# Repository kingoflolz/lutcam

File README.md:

# LUTCam - FPGA image fiducial detection

**Note, this repo is just a snapshot of a side project. Don't expect any support or new features.**

**All the software/RTL is AI generated, but it does work ¯\\\_(ツ)\_/¯**

See blog post describing this project [here](https://benwang.dev/2026/11/01/FPGA-Fiducial.html).

LUTCam's original RTL/gateware, software, firmware, and hardware designs are
licensed under the [Apache License, Version 2.0](LICENSE). See [NOTICE](NOTICE)
for the scope and [THIRD_PARTY_NOTICES.md](THIRD_PARTY_NOTICES.md) for third-party
code, library elements, models, documentation, and data that retain their own terms.

The project is organized into three directories:

| Directory | Contents |
| --- | --- |
| [software](software/) | Camera viewer, reusable Rust libraries, and their software tests |
| [hardware](hardware/) | KiCad board and schematics, local libraries, 3D models, and datasheets |
| [gateware](gateware/) | Production RTL, FPGA targets, Rust reference models and RTL tests, Python simulations, board tools, fixtures, and design documentation |

One root `Cargo.toml` and `Cargo.lock` cover both software and gateware crates.
The default members are the four software crates; RTL verification crates are
selected explicitly or with `--workspace`.

Run these commands from the repository root:

```sh
cargo run --locked -p lutcam-viewer --release
cargo test --locked                                      # Software tests
cargo test --locked -p lrcca-rtl-tests -- --test-threads=1 # LRCCA RTL tests
cargo test --locked --workspace -- --test-threads=1       # All Rust tests
```

Run FPGA builds, Python board helpers, and HDL checks from `gateware`.
See the [gateware guide](gateware/README.md),
[board build setup](gateware/README.md#toolchain), and
[viewer guide](software/crates/lutcam-viewer/README.md).
Open [hardware/lutcam-hardware.kicad_pro](hardware/lutcam-hardware.kicad_pro)
in KiCad to work on the board.

The software and gateware directories depend on each other; keep them as
siblings. The LiteX Python environment is defined in `gateware/pyproject.toml`
and `gateware/uv.lock`; run `uv sync --locked` from `gateware` to create it.
LUNA, its LiteX wrapper, and LiteEth are vendored with the required fixes under
`gateware/vendor`; the build uses them by default.
The viewer uses `gateware/.venv/bin/python`
when available, otherwise `python3`.

Version control contains the current sources, dependency locks, required ROM
tables, test fixtures, component models, and design documentation. Build products,
captures, benchmark output, fabrication exports, historical snapshots, editor
state, and backups are local artifacts excluded by `.gitignore`.

Repository paths are relative to the documented working directory or resolved
from the calling script's location. Set `EFINITY_HOME` (or `LITEX_ENV_EFINITY`
for LiteX) to your external Efinity installation when running native FPGA tools
or vendor-model tests.

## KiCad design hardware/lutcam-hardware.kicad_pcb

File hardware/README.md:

# Lutcam hardware

Open `lutcam-hardware.kicad_pro` in KiCad to work on the board and schematics.
The [datasheet inventory](datasheets/README.md) and
[3D model provenance](models3d/README.md) describe the supporting assets.

## License

Lutcam's original hardware design files, including schematics, PCB layout,
original symbols and footprints, and original mechanical models, are licensed
under the [Apache License, Version 2.0](../LICENSE).

Third-party library elements, supplier models, and manufacturer documentation
retain their own terms, including when embedded in a design or converted to
another format. See [NOTICE](../NOTICE) and
[THIRD_PARTY_NOTICES.md](../THIRD_PARTY_NOTICES.md) for the scope and exceptions.

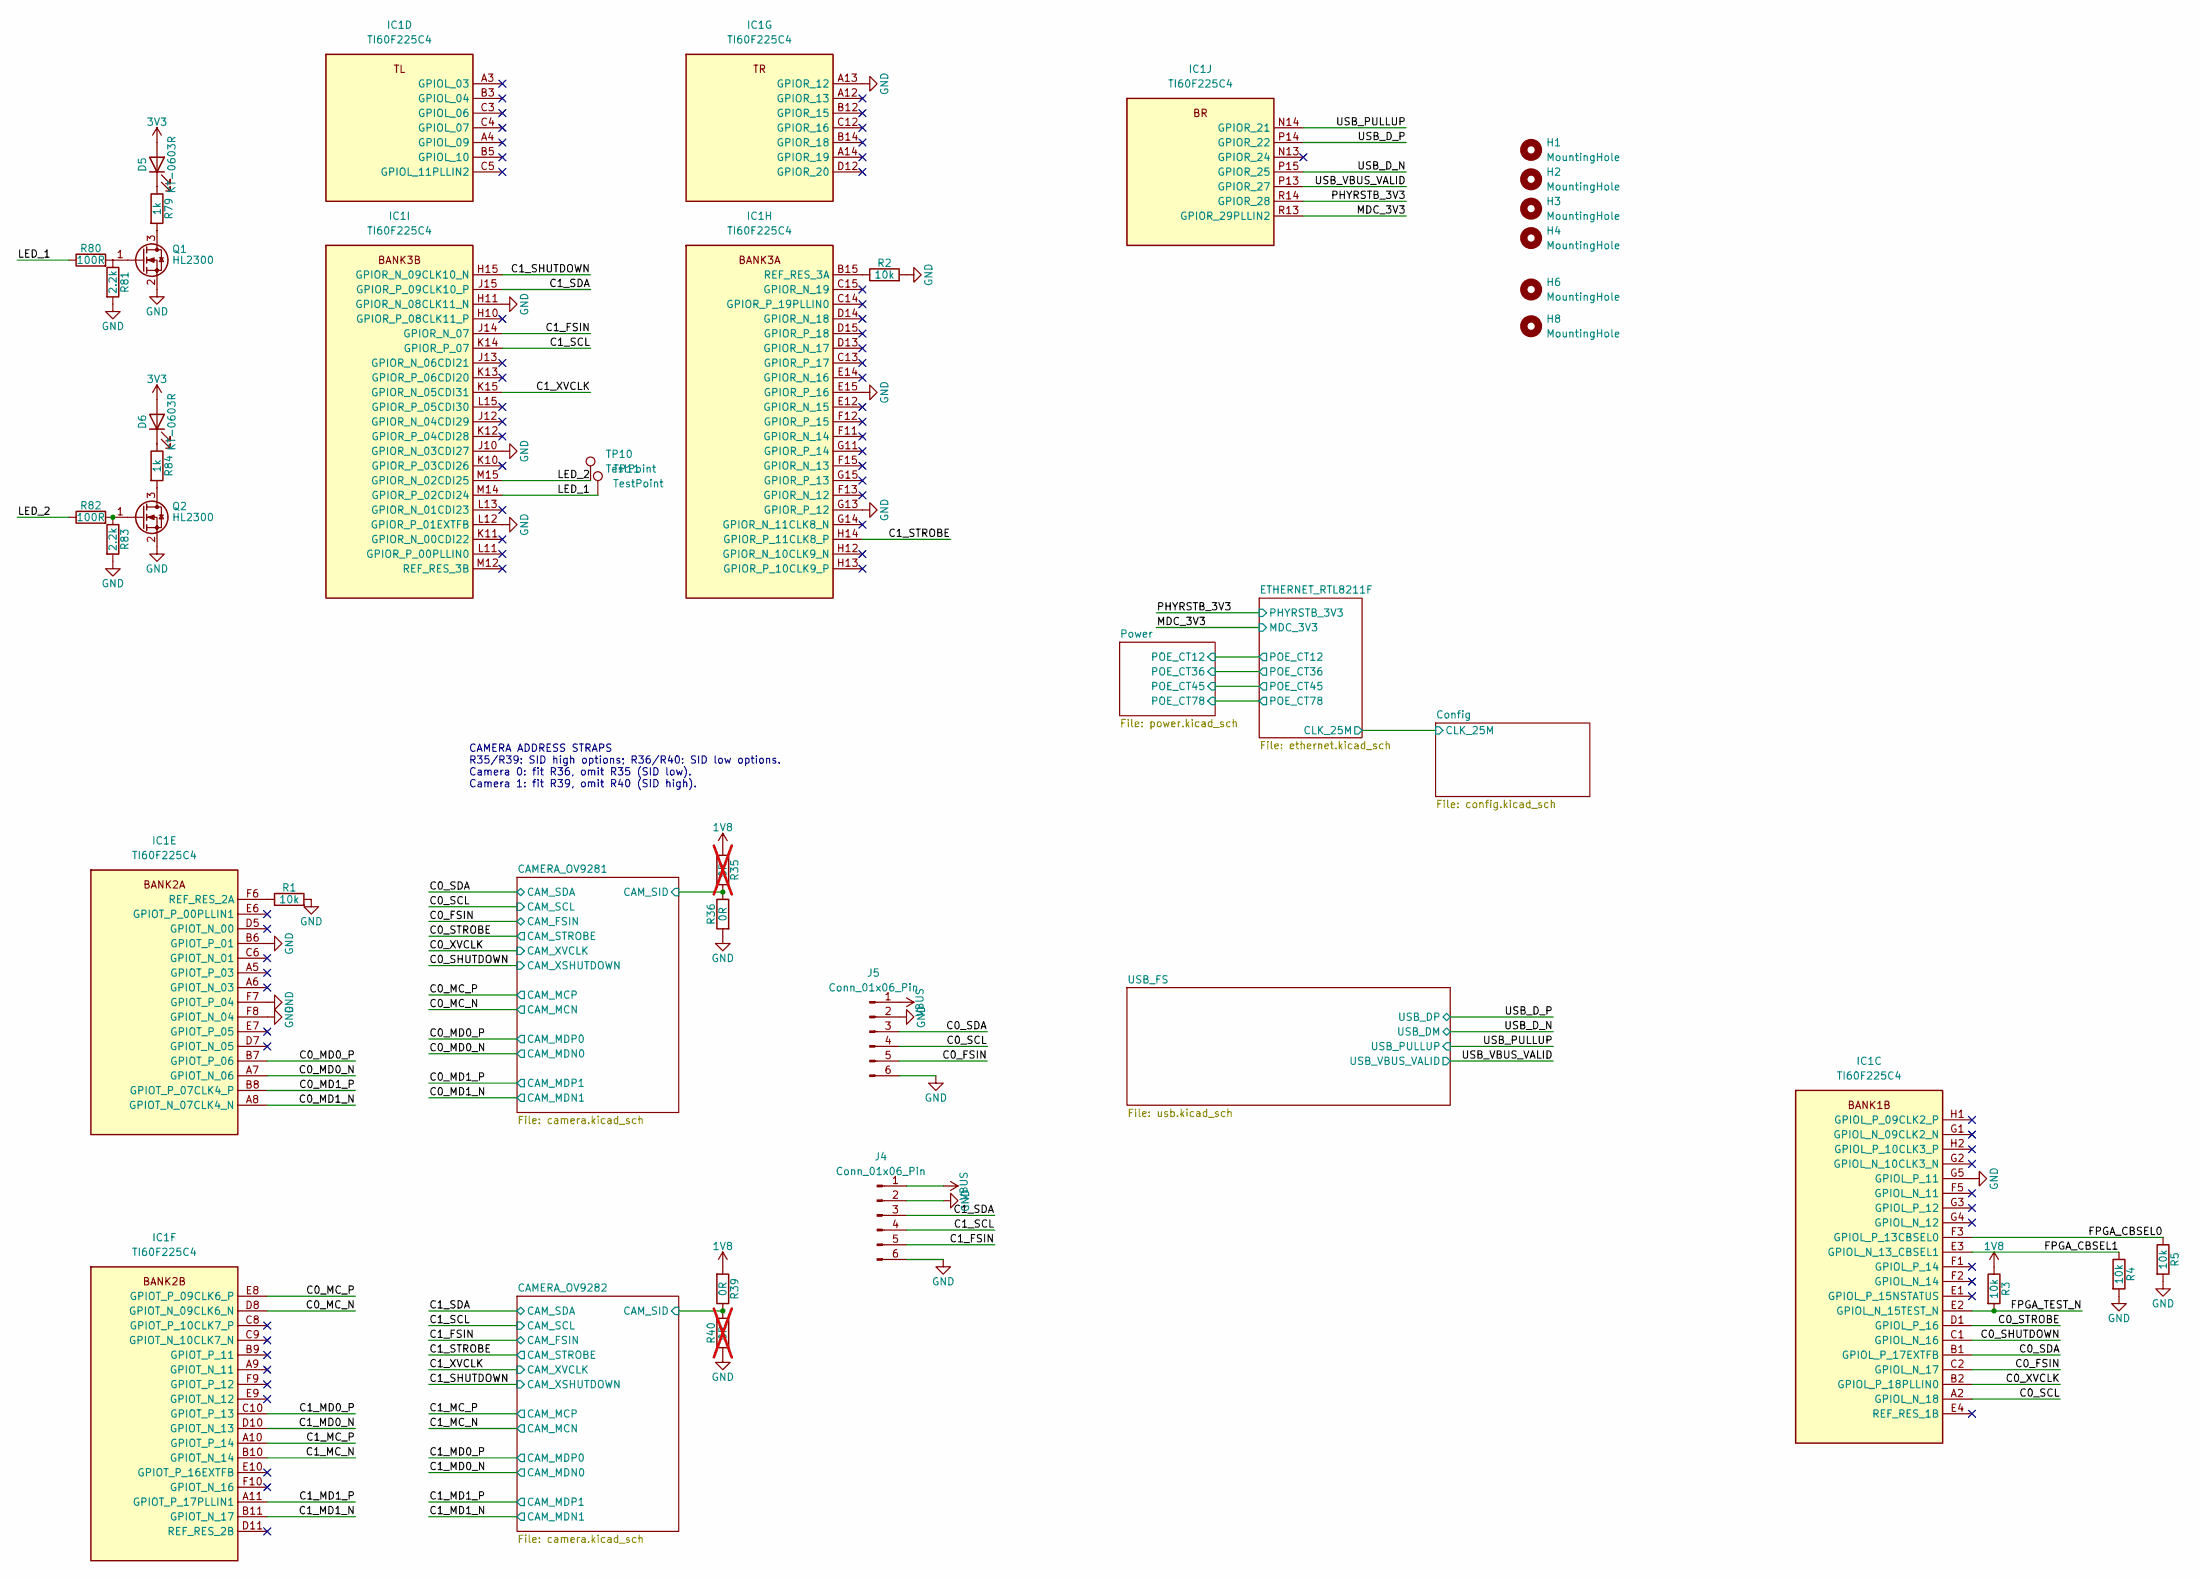
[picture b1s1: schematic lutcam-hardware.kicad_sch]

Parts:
D5, D6: KT-0603R; LED_0603_1608Metric; MPN KT-0603R; JLCPCB Library Basic
H1, H2, H3, H4, H6: MountingHole; MountingHole_2.2mm_M2_Pad_Via
H8: MountingHole; ToolingHole_1.152mm
IC1: TI60F225C4; BGA225C65P15X15_1000X1000X100; Manufacturer_Part_Number TI60F225C4
J4, J5: Conn_01x06_Pin; PinHeader_1x06_P2.54mm_Vertical
Q1, Q2: HL2300; SOT-23; MPN HL2300; JLCPCB Library Promotional Extended
R1, R2, R3, R4, R5: 10k; R_0402_1005Metric; MPN 0402WGF1002TCE; JLCPCB Library Basic
R35, R40: 0R; R_0402_1005Metric; MPN 0402WGF0000TCE; JLCPCB Library Basic; not fitted
R36, R39: 0R; R_0402_1005Metric; MPN 0402WGF0000TCE; JLCPCB Library Basic
R79, R84: 1k; R_0402_1005Metric; MPN 0402WGF1001TCE; JLCPCB Library Basic
R80, R82: 100R; R_0402_1005Metric; MPN 0402WGF1000TCE; JLCPCB Library Basic
R81, R83: 2.2k; R_0402_1005Metric; MPN 0402WGF2201TCE; JLCPCB Library Basic
TP10, TP11: TestPoint; TestPoint_Pad_D2.0mm

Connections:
1V8: R3.1, R35.2, R39.2; also elsewhere on the board
3V3: D5.2 (A), D6.2 (A); also elsewhere on the board
/C0_FSIN: IC1.C2 (GPIOL_N_17), J5.5; also elsewhere on the board
/C0_MC_N: IC1.D8 (GPIOT_N_09CLK6_N); also elsewhere on the board
/C0_MC_P: IC1.E8 (GPIOT_P_09CLK6_P); also elsewhere on the board
/C0_MD0_N: IC1.A7 (GPIOT_N_06); also elsewhere on the board
/C0_MD0_P: IC1.B7 (GPIOT_P_06); also elsewhere on the board
/C0_MD1_N: IC1.A8 (GPIOT_N_07CLK4_N); also elsewhere on the board
/C0_MD1_P: IC1.B8 (GPIOT_P_07CLK4_P); also elsewhere on the board
/C0_SCL: IC1.A2 (GPIOL_N_18), J5.4; also elsewhere on the board
/C0_SDA: IC1.B1 (GPIOL_P_17EXTFB), J5.3; also elsewhere on the board
/C0_SHUTDOWN: IC1.C1 (GPIOL_N_16); also elsewhere on the board
/C0_STROBE: IC1.D1 (GPIOL_P_16); also elsewhere on the board
/C0_XVCLK: IC1.B2 (GPIOL_P_18PLLIN0); also elsewhere on the board
/C1_FSIN: IC1.J14 (GPIOR_N_07), J4.5; also elsewhere on the board
/C1_MC_N: IC1.B10 (GPIOT_N_14); also elsewhere on the board
/C1_MC_P: IC1.A10 (GPIOT_P_14); also elsewhere on the board
/C1_MD0_N: IC1.D10 (GPIOT_N_13); also elsewhere on the board
/C1_MD0_P: IC1.C10 (GPIOT_P_13); also elsewhere on the board
/C1_MD1_N: IC1.B11 (GPIOT_N_17); also elsewhere on the board
/C1_MD1_P: IC1.A11 (GPIOT_P_17PLLIN1); also elsewhere on the board
/C1_SCL: IC1.K14 (GPIOR_P_07), J4.4; also elsewhere on the board
/C1_SDA: IC1.J15 (GPIOR_P_09CLK10_P), J4.3; also elsewhere on the board
/C1_SHUTDOWN: IC1.H15 (GPIOR_N_09CLK10_N); also elsewhere on the board
/C1_STROBE: IC1.H14 (GPIOR_P_11CLK8_P); also elsewhere on the board
/C1_XVCLK: IC1.K15 (GPIOR_N_05CDI31); also elsewhere on the board
/CAMERA_OV9281/CAM_SID: R35.1, R36.1; also elsewhere on the board
/CAMERA_OV9282/CAM_SID: R39.1, R40.1; also elsewhere on the board
/FPGA_CBSEL0: IC1.F3 (GPIOL_P_13CBSEL0), R5.1
/FPGA_CBSEL1: IC1.E3 (GPIOL_N_13_CBSEL1), R4.1
/FPGA_TEST_N: IC1.E2 (GPIOL_N_15TEST_N), R3.2
/LED_1: IC1.M14 (GPIOR_P_02CDI24), R80.1, TP11.1 (1_1)
/LED_2: IC1.M15 (GPIOR_N_02CDI25), R82.1, TP10.1 (1_1)
/MDC_3V3: IC1.R13 (GPIOR_29PLLIN2); also elsewhere on the board
/PHYRSTB_3V3: IC1.R14 (GPIOR_28); also elsewhere on the board
/USB_D_N: IC1.P15 (GPIOR_25); also elsewhere on the board
/USB_D_P: IC1.P14 (GPIOR_22); also elsewhere on the board
/USB_PULLUP: IC1.N14 (GPIOR_21); also elsewhere on the board
/USB_VBUS_VALID: IC1.P13 (GPIOR_27); also elsewhere on the board
GND: IC1.A13 (GPIOR_12), IC1.B6 (GPIOT_P_01), IC1.E15 (GPIOR_P_16), IC1.F7 (GPIOT_P_04), IC1.F8 (GPIOT_N_04), IC1.G5 (GPIOL_P_11), IC1.G13 (GPIOR_P_12), IC1.H11 (GPIOR_N_08CLK11_N), IC1.J10 (GPIOR_N_03CDI27), IC1.L12 (GPIOR_P_01EXTFB), J4.2, J4.6, J5.2, J5.6, Q1.2 (S), Q2.2 (S), R1.2, R2.2, R4.2, R5.2, R36.2, R40.2, R81.2, R83.2; also elsewhere on the board
unnamed: D5.1 (K), R79.1
unnamed: D6.1 (K), R84.1
unnamed: IC1.F6 (REF_RES_2A), R1.1
unnamed: IC1.B15 (REF_RES_3A), R2.1
unnamed: Q1.3 (D), R79.2
unnamed: Q1.1 (G), R80.2, R81.1
unnamed: Q2.3 (D), R84.2
unnamed: Q2.1 (G), R82.2, R83.1
VBUS: J4.1, J5.1; also elsewhere on the board

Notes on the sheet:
CAMERA ADDRESS STRAPS R35/R39: SID high options; R36/R40: SID low options. Camera 0: fit R36, omit R35 (SID low). Camera 1: fit R39, omit R40 (SID high).

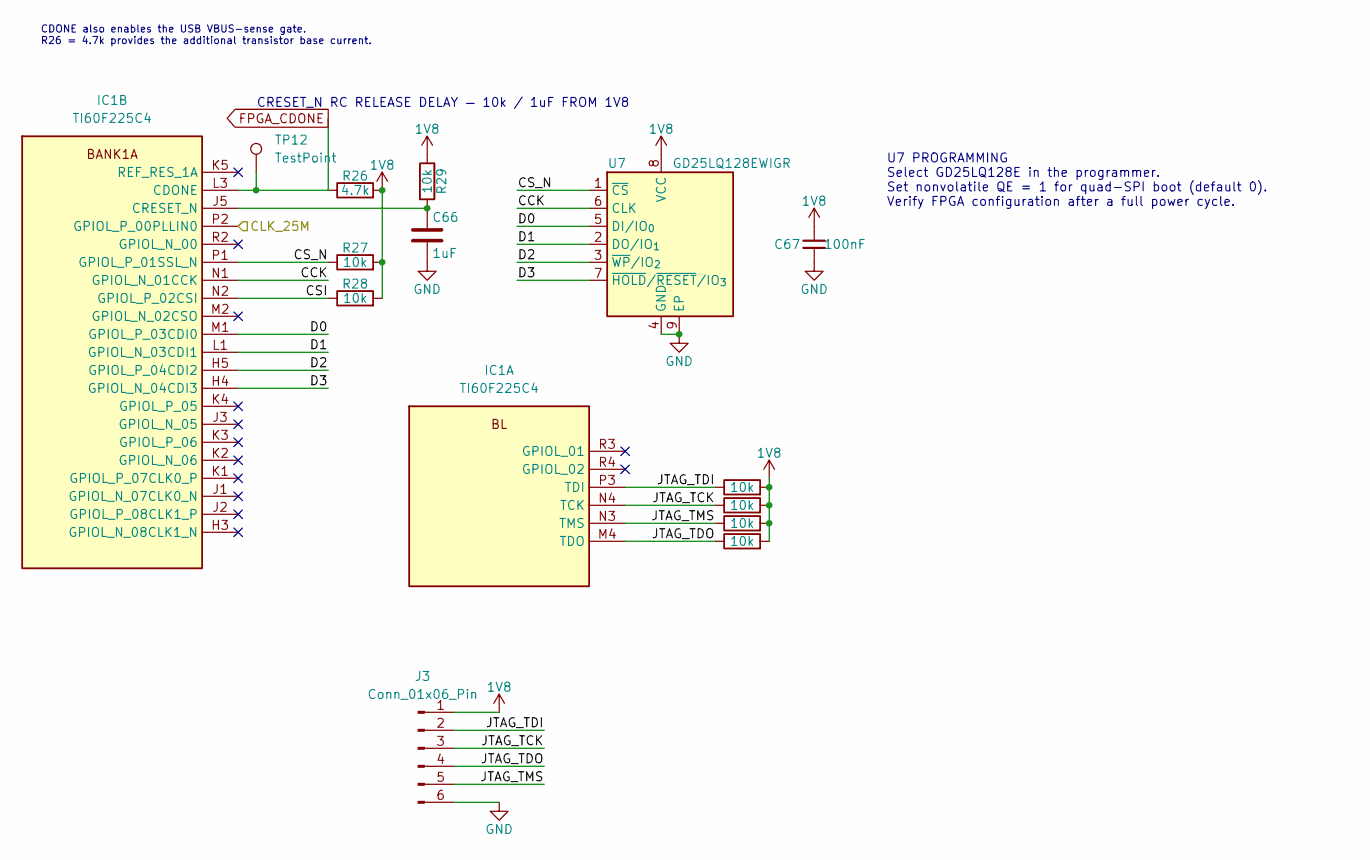
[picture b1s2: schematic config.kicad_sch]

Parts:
C66: 1uF; C_0402_1005Metric; MPN CL05A105KA5NQNC; JLCPCB Library Basic
C67: 100nF; C_0402_1005Metric; MPN CL05B104KO5NNNC; JLCPCB Library Basic
IC1: TI60F225C4; BGA225C65P15X15_1000X1000X100; Manufacturer_Part_Number TI60F225C4
J3: Conn_01x06_Pin; PinHeader_1x06_P2.54mm_Vertical
R26: 4.7k; R_0402_1005Metric; MPN 0402WGF4701TCE; JLCPCB Library Basic
R27, R28, R29, R30, R31, R32, R33: 10k; R_0402_1005Metric; MPN 0402WGF1002TCE; JLCPCB Library Basic
TP12: TestPoint; TestPoint_Pad_D2.0mm
U7: GD25LQ128EWIGR; WSON-8-1EP_6x5mm_P1.27mm_EP3.4x4.3mm; MPN GD25LQ128EWIGR; LCSC C2928889

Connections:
1V8: C67.2, J3.1, R26.2, R27.2, R28.2, R29.1, R30.2, R31.2, R32.2, R33.2, U7.8 (VCC); also elsewhere on the board
/Config/CCK: IC1.N1 (GPIOL_N_01CCK), U7.6 (CLK)
/Config/CLK_25M: IC1.P2 (GPIOL_P_00PLLIN0); also elsewhere on the board
/Config/CSI: IC1.N2 (GPIOL_P_02CSI), R28.1
/Config/CS_N: IC1.P1 (GPIOL_P_01SSL_N), R27.1, U7.1 (~CS)
/Config/D0: IC1.M1 (GPIOL_P_03CDI0), U7.5 (DI/IO_{0})
/Config/D1: IC1.L1 (GPIOL_N_03CDI1), U7.2 (DO/IO_{1})
/Config/D2: IC1.H5 (GPIOL_P_04CDI2), U7.3 (~WP/IO_{2})
/Config/D3: IC1.H4 (GPIOL_N_04CDI3), U7.7 (~HOLD/~RESET/IO_{3})
/Config/JTAG_TCK: IC1.N4 (TCK), J3.3, R31.1
/Config/JTAG_TDI: IC1.P3 (TDI), J3.2, R30.1
/Config/JTAG_TDO: IC1.M4 (TDO), J3.4, R33.1
/Config/JTAG_TMS: IC1.N3 (TMS), J3.5, R32.1
FPGA_CDONE: IC1.L3 (CDONE), R26.1, TP12.1 (1_1); also elsewhere on the board
GND: C66.2, C67.1, J3.6, U7.4 (GND), U7.9 (EP); also elsewhere on the board
unnamed: C66.1, IC1.J5 (CRESET_N), R29.2

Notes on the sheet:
CRESET_N RC RELEASE DELAY — 10k / 1uF FROM 1V8
U7 PROGRAMMING Select GD25LQ128E in the programmer. Set nonvolatile QE = 1 for quad-SPI boot (default 0). Verify FPGA configuration after a full power cycle.
CDONE also enables the USB VBUS-sense gate. R26 = 4.7k provides the additional transistor base current.

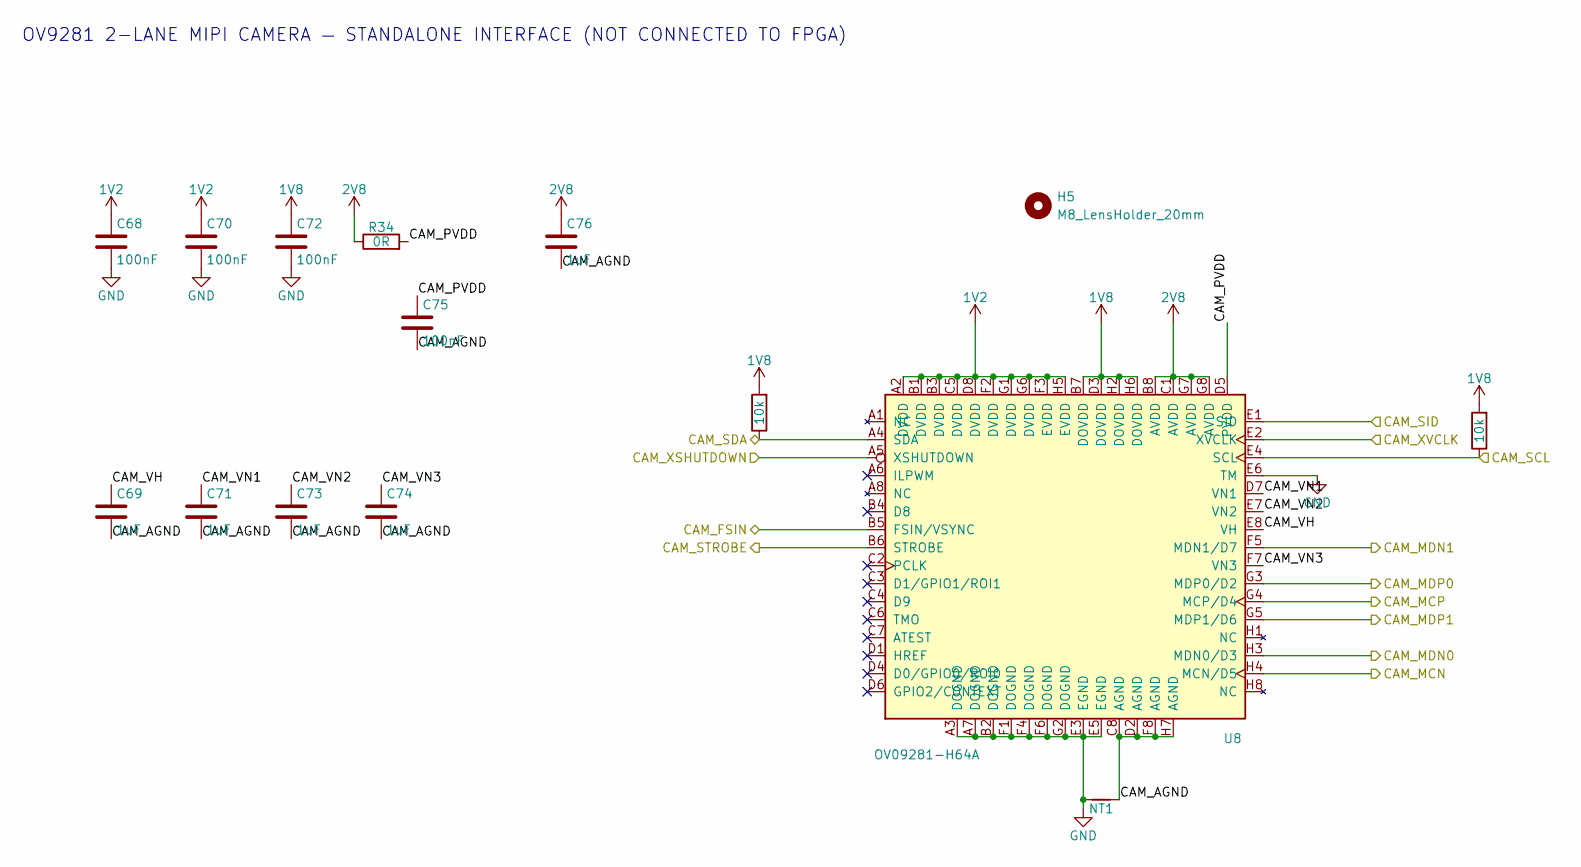
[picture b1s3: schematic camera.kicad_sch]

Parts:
C68, C70, C72, C75: 100nF; C_0402_1005Metric; MPN CL05B104KO5NNNC; JLCPCB Library Basic
C69, C71, C73, C74, C76: 1uF; C_0402_1005Metric; MPN CL05A105KA5NQNC; JLCPCB Library Basic
H5: M8_LensHolder_20mm; MountingHole_M8_LensHolder_P20mm_2xM2_Pad_Via
NT1: CAM_AGND-GND; NetTie-2_SMD_Pad0.5mm
R34: 0R; R_0402_1005Metric; MPN 0402WGF0000TCE; JLCPCB Library Basic
R212, R213: 10k; R_0402_1005Metric; MPN 0402WGF1002TCE; JLCPCB Library Basic
U8: OV09281-H64A; OmniVision_CSP-64_5.237x4.463mm_Layout8x8_P0.64x0.50mm; MPN OV09281-H64A

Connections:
1V2: C68.1, C70.1, U8.A2 (DVDD), U8.B1 (DVDD), U8.B3 (DVDD), U8.C5 (DVDD), U8.D8 (DVDD), U8.F2 (DVDD), U8.F3 (EVDD), U8.G1 (DVDD), U8.G6 (DVDD), U8.H5 (EVDD); also elsewhere on the board
1V8: C72.1, R212.2, R213.2, U8.B7 (DOVDD), U8.D3 (DOVDD), U8.H2 (DOVDD), U8.H6 (DOVDD); also elsewhere on the board
2V8: C76.1, R34.1, U8.B8 (AVDD), U8.C1 (AVDD), U8.G7 (AVDD), U8.G8 (AVDD); also elsewhere on the board
/C0_FSIN: U8.B5 (FSIN/VSYNC); also elsewhere on the board
/C0_MC_N: U8.H4 (MCN/D5); also elsewhere on the board
/C0_MC_P: U8.G4 (MCP/D4); also elsewhere on the board
/C0_MD0_N: U8.H3 (MDN0/D3); also elsewhere on the board
/C0_MD0_P: U8.G3 (MDP0/D2); also elsewhere on the board
/C0_MD1_N: U8.F5 (MDN1/D7); also elsewhere on the board
/C0_MD1_P: U8.G5 (MDP1/D6); also elsewhere on the board
/C0_SCL: R213.1, U8.E4 (SCL); also elsewhere on the board
/C0_SDA: R212.1, U8.A4 (SDA); also elsewhere on the board
/C0_SHUTDOWN: U8.A5 (XSHUTDOWN); also elsewhere on the board
/C0_STROBE: U8.B6 (STROBE); also elsewhere on the board
/C0_XVCLK: U8.E2 (XVCLK); also elsewhere on the board
/CAMERA_OV9281/CAM_AGND: C69.2, C71.2, C73.2, C74.2, C75.2, C76.2, NT1.1, U8.C8 (AGND), U8.D2 (AGND), U8.F8 (AGND), U8.H7 (AGND)
/CAMERA_OV9281/CAM_PVDD: C75.1, R34.2, U8.D5 (PVDD)
/CAMERA_OV9281/CAM_SID: U8.E1 (SID); also elsewhere on the board
/CAMERA_OV9281/CAM_VH: C69.1, U8.E8 (VH)
/CAMERA_OV9281/CAM_VN1: C71.1, U8.D7 (VN1)
/CAMERA_OV9281/CAM_VN2: C73.1, U8.E7 (VN2)
/CAMERA_OV9281/CAM_VN3: C74.1, U8.F7 (VN3)
GND: C68.2, C70.2, C72.2, NT1.2, U8.A3 (DOGND), U8.A7 (DOGND), U8.B2 (DOGND), U8.E3 (EGND), U8.E5 (EGND), U8.E6 (TM), U8.F1 (DOGND), U8.F4 (DOGND), U8.F6 (DOGND), U8.G2 (DOGND); also elsewhere on the board

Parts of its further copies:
C95, C97, C99, C102: 100nF; C_0402_1005Metric; MPN CL05B104KO5NNNC; JLCPCB Library Basic
C96, C98, C100, C101, C103: 1uF; C_0402_1005Metric; MPN CL05A105KA5NQNC; JLCPCB Library Basic
H7: M8_LensHolder_20mm; MountingHole_M8_LensHolder_P20mm_2xM2_Pad_Via
NT2: CAM_AGND-GND; NetTie-2_SMD_Pad0.5mm
R78: 0R; R_0402_1005Metric; MPN 0402WGF0000TCE; JLCPCB Library Basic
R214, R215: 10k; R_0402_1005Metric; MPN 0402WGF1002TCE; JLCPCB Library Basic
U11: OV09281-H64A; OmniVision_CSP-64_5.237x4.463mm_Layout8x8_P0.64x0.50mm; MPN OV09281-H64A

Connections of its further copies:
1V2: C95.1, C97.1, U11.A2 (DVDD), U11.B1 (DVDD), U11.B3 (DVDD), U11.C5 (DVDD), U11.D8 (DVDD), U11.F2 (DVDD), U11.F3 (EVDD), U11.G1 (DVDD), U11.G6 (DVDD), U11.H5 (EVDD); also elsewhere on the board
1V8: C99.1, R214.2, R215.2, U11.B7 (DOVDD), U11.D3 (DOVDD), U11.H2 (DOVDD), U11.H6 (DOVDD); also elsewhere on the board
2V8: C103.1, R78.1, U11.B8 (AVDD), U11.C1 (AVDD), U11.G7 (AVDD), U11.G8 (AVDD); also elsewhere on the board
/C1_FSIN: U11.B5 (FSIN/VSYNC); also elsewhere on the board
/C1_MC_N: U11.H4 (MCN/D5); also elsewhere on the board
/C1_MC_P: U11.G4 (MCP/D4); also elsewhere on the board
/C1_MD0_N: U11.H3 (MDN0/D3); also elsewhere on the board
/C1_MD0_P: U11.G3 (MDP0/D2); also elsewhere on the board
/C1_MD1_N: U11.F5 (MDN1/D7); also elsewhere on the board
/C1_MD1_P: U11.G5 (MDP1/D6); also elsewhere on the board
/C1_SCL: R215.1, U11.E4 (SCL); also elsewhere on the board
/C1_SDA: R214.1, U11.A4 (SDA); also elsewhere on the board
/C1_SHUTDOWN: U11.A5 (XSHUTDOWN); also elsewhere on the board
/C1_STROBE: U11.B6 (STROBE); also elsewhere on the board
/C1_XVCLK: U11.E2 (XVCLK); also elsewhere on the board
/CAMERA_OV9282/CAM_AGND: C96.2, C98.2, C100.2, C101.2, C102.2, C103.2, NT2.1, U11.C8 (AGND), U11.D2 (AGND), U11.F8 (AGND), U11.H7 (AGND)
/CAMERA_OV9282/CAM_PVDD: C102.1, R78.2, U11.D5 (PVDD)
/CAMERA_OV9282/CAM_SID: U11.E1 (SID); also elsewhere on the board
/CAMERA_OV9282/CAM_VH: C96.1, U11.E8 (VH)
/CAMERA_OV9282/CAM_VN1: C98.1, U11.D7 (VN1)
/CAMERA_OV9282/CAM_VN2: C100.1, U11.E7 (VN2)
/CAMERA_OV9282/CAM_VN3: C101.1, U11.F7 (VN3)
GND: C95.2, C97.2, C99.2, NT2.2, U11.A3 (DOGND), U11.A7 (DOGND), U11.B2 (DOGND), U11.E3 (EGND), U11.E5 (EGND), U11.E6 (TM), U11.F1 (DOGND), U11.F4 (DOGND), U11.F6 (DOGND), U11.G2 (DOGND); also elsewhere on the board

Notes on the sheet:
OV9281 2-LANE MIPI CAMERA — STANDALONE INTERFACE (NOT CONNECTED TO FPGA)

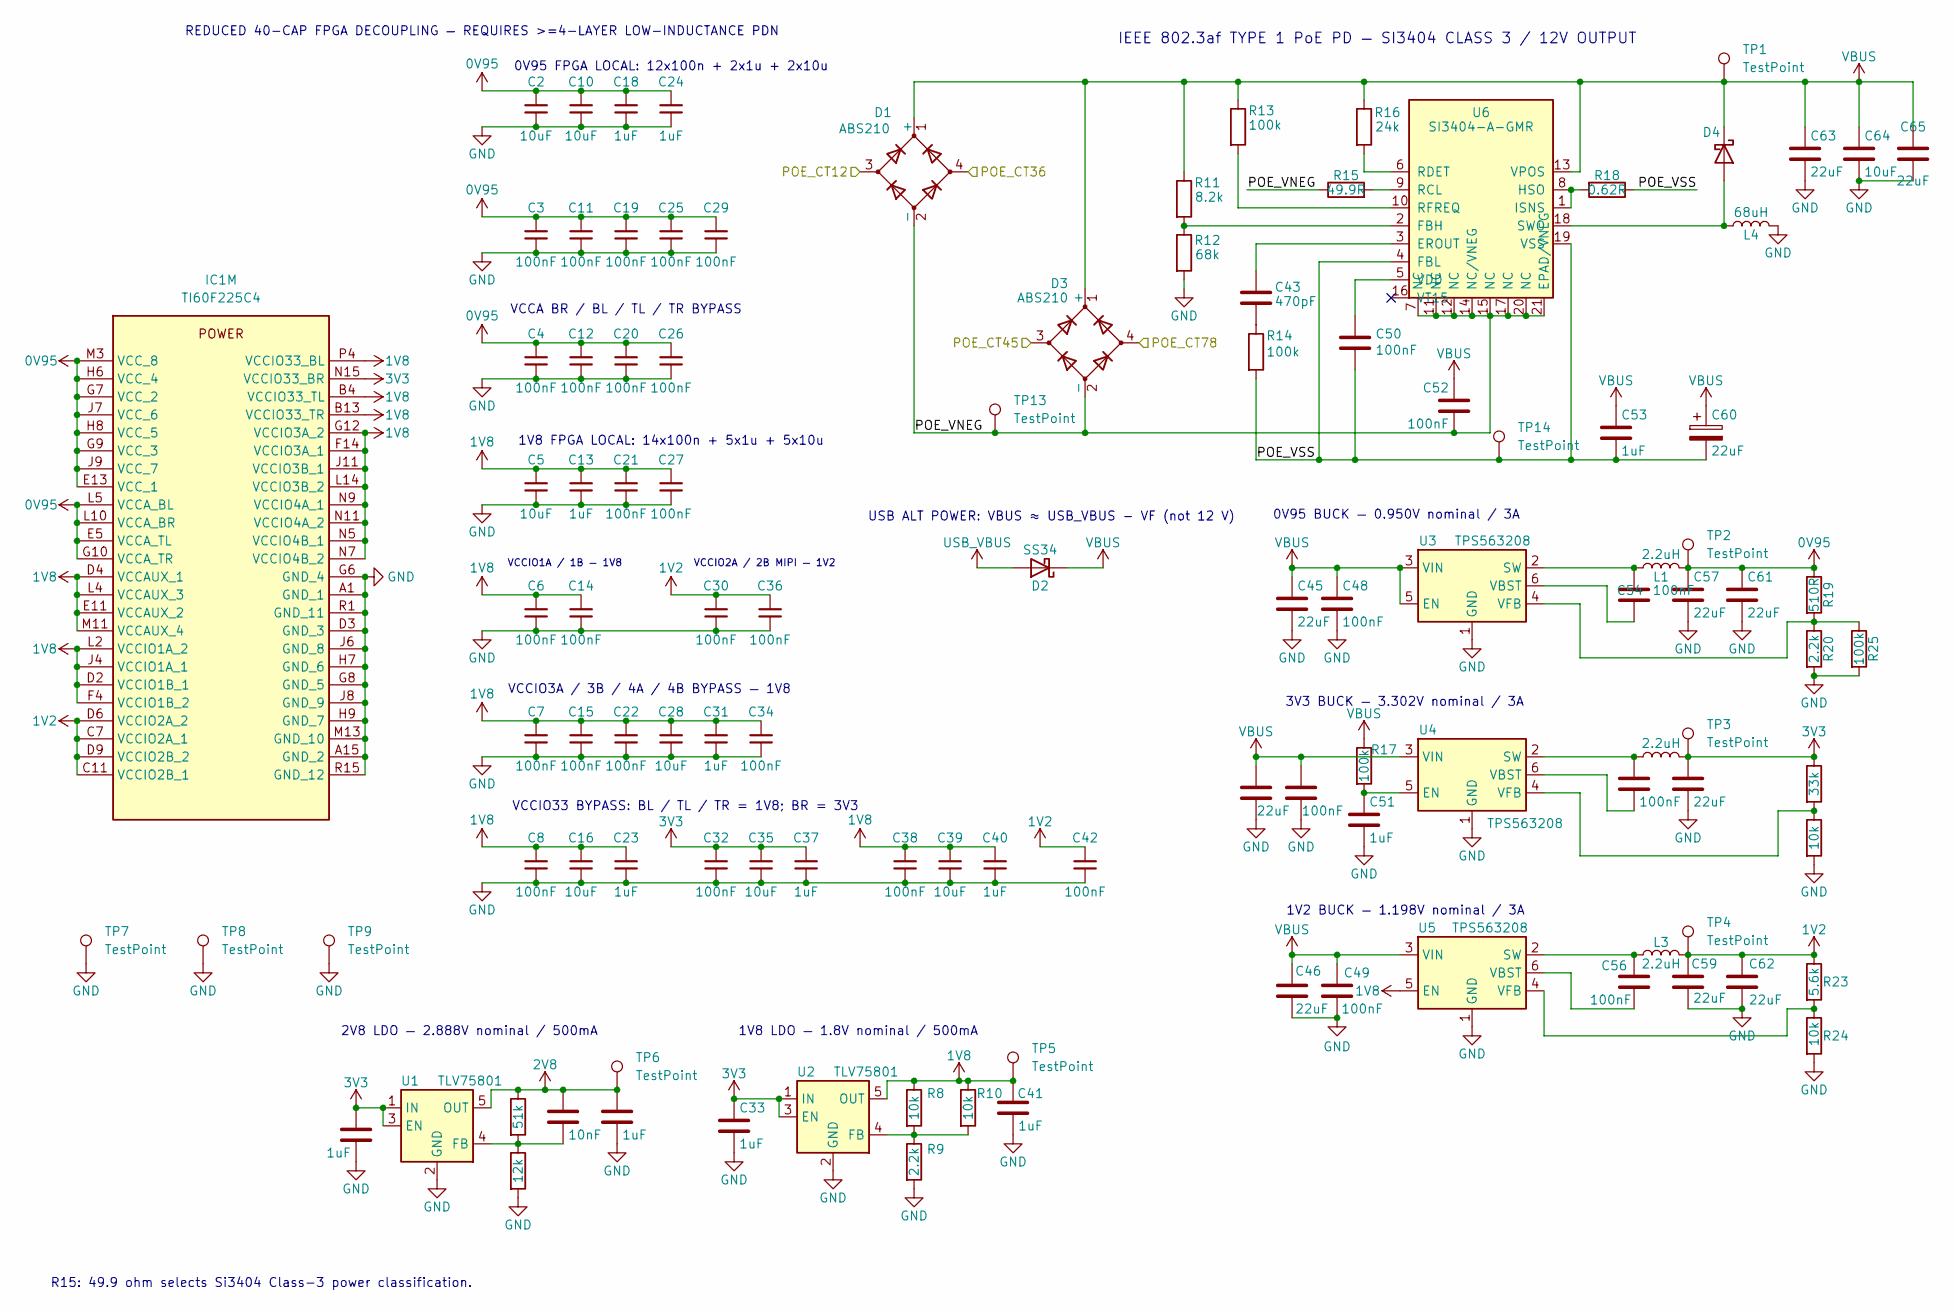
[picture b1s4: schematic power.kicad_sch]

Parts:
C1, C17, C33, C41, C51: 1uF; C_0402_1005Metric; MPN CL05A105KA5NQNC; LCSC C52923
C2, C5, C10, C16, C28, C35, C39: 10uF; C_0603_1608Metric; MPN CL10A106KP8NNNC; JLCPCB Library Basic
C3, C4, C6, C7, C11, C12, C14, C15, C19, C20, C21, C22, C25, C26, C27, C29, C30, C32, C34, C36, C38, C42: 100nF; C_0402_1005Metric; MPN CL05B104KO5NNNC; JLCPCB Library Basic
C8, C54, C55, C56: 100nF; C_0402_1005Metric; MPN CL05B104KO5NNNC; LCSC C1525
C9: 10nF; C_0402_1005Metric; MPN CL05B103KB5NNNC; LCSC C15195
C13, C18, C23, C24, C31, C37, C40: 1uF; C_0402_1005Metric; MPN CL05A105KA5NQNC; JLCPCB Library Basic
C43: 470pF; C_0402_1005Metric; MPN 0402B471K500NT; LCSC C1537
C44, C45, C46, C63, C65: 22uF; C_1206_3216Metric; MPN CL31A226KAHNNNE; LCSC C12891
C47, C48, C49, C50: 100nF; C_0402_1005Metric; MPN CL05B104KB54PNC; LCSC C307331
C52: 100nF; C_0805_2012Metric; MPN CL21B104KCFNNNE; LCSC C28233
C53: 1uF; C_1210_3225Metric; MPN CL32B105KCJNNNE; LCSC C444847
C57, C59, C61, C62: 22uF; C_0603_1608Metric; MPN CL10A226MQ8NRNC; LCSC C59461
C58: 22uF; C_0805_2012Metric; MPN CL21A226MAQNNNE; LCSC C45783
C60: 22uF; CP_Elec_6.3x9.9; MPN VKMC1002A220MV; LCSC C487431
C64: 10uF; C_0805_2012Metric; MPN CL21A106KAYNNNE; LCSC C15850
D1, D3: ABS210; ABS_4P_L5.0-W4.4_P4.10x5.81mm; MPN ABS210; LCSC C42406052
D2: SS34; D_SMA; MPN SS34; LCSC C8678
D4: PDS3100-13; D_PowerDI-5; MPN PDS3100-13; LCSC C154881
IC1: TI60F225C4; BGA225C65P15X15_1000X1000X100; Manufacturer_Part_Number TI60F225C4
L1, L2, L3: 2.2uH; L_Changjiang_FTC252012S; MPN FTC252012S2R2MBCA; LCSC C5832372
L4: 68uH; L_PROD_PSPMAA0605H_7.1x6.6mm; MPN PSPMAA0605H-680M-ANP; LCSC C49308193
R6: 51k; R_0402_1005Metric; MPN 0402WGF5102TCE; LCSC C25794
R7: 12k; R_0402_1005Metric; MPN 0402WGF1202TCE; LCSC C25752
R8, R22, R24: 10k; R_0402_1005Metric; MPN 0402WGF1002TCE; LCSC C25744
R9, R20: 2.2k; R_0402_1005Metric; MPN 0402WGF2201TCE; LCSC C25879
R10: 10k; R_0402_1005Metric; MPN 0402WGF1002TCE; JLCPCB Library Basic
R11: 8.2k; R_0402_1005Metric; MPN 0402WGF8201TCE; LCSC C25924
R12: 68k; R_0402_1005Metric; MPN 0402WGF6802TCE; LCSC C36871
R13, R14, R17: 100k; R_0402_1005Metric; MPN 0402WGF1003TCE; LCSC C25741
R15: 49.9R; R_0402_1005Metric; MPN 0402WGF499JTCE; LCSC C25120
R16: 24k; R_0402_1005Metric; MPN 0402WGF2402TCE; LCSC C25769
R18: 0.62R; R_0805_2012Metric; MPN FRL0805FR620TS; LCSC C2930222
R19: 510R; R_0402_1005Metric; MPN 0402WGF5100TCE; LCSC C25123
R21: 33k; R_0402_1005Metric; MPN 0402WGF3302TCE; LCSC C25779
R23: 5.6k; R_0402_1005Metric; MPN 0402WGF5601TCE; LCSC C25908
R25: 100k; R_0402_1005Metric; MPN 0402WGF1003TCE; JLCPCB Library Basic
TP1, TP2, TP3, TP4, TP5, TP6, TP7, TP8, TP9, TP13, TP14: TestPoint; TestPoint_Pad_D2.0mm
U1, U2: TLV75801; SOT-23-5; MPN TLV75801PDBVR; LCSC C2877852
U3, U4, U5: TPS563208; TSOT-23-6; MPN TPS563208DDCR; LCSC C468250
U6: SI3404-A-GMR; Skyworks_QFN-20-1EP_4x4mm_P0.5mm_EP2.6x2.6mm_NoVias; MPN SI3404-A-GMR; LCSC C461934

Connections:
0V95: C2.1, C3.1, C4.1, C10.1, C11.1, C12.1, C18.1, C19.1, C20.1, C24.1, C25.1, C26.1, C29.1, C57.1, C61.1, IC1.E5 (VCCA_TL), IC1.E13 (VCC_1), IC1.G7 (VCC_2), IC1.G9 (VCC_3), IC1.G10 (VCCA_TR), IC1.H6 (VCC_4), IC1.H8 (VCC_5), IC1.J7 (VCC_6), IC1.J9 (VCC_7), IC1.L5 (VCCA_BL), IC1.L10 (VCCA_BR), IC1.M3 (VCC_8), L1.2, R19.1, TP2.1 (1_1)
1V2: C30.1, C36.1, C42.1, C59.1, C62.1, IC1.C7 (VCCIO2A_1), IC1.C11 (VCCIO2B_1), IC1.D6 (VCCIO2A_2), IC1.D9 (VCCIO2B_2), L3.2, R23.1, TP4.1 (1_1); also elsewhere on the board
1V8: C5.1, C6.1, C7.1, C8.1, C13.1, C14.1, C15.1, C16.1, C21.1, C22.1, C23.1, C27.1, C28.1, C31.1, C34.1, C38.1, C39.1, C40.1, C41.1, IC1.B4 (VCCIO33_TL), IC1.B13 (VCCIO33_TR), IC1.D2 (VCCIO1B_1), IC1.D4 (VCCAUX_1), IC1.E11 (VCCAUX_2), IC1.F4 (VCCIO1B_2), IC1.F14 (VCCIO3A_1), IC1.G12 (VCCIO3A_2), IC1.J4 (VCCIO1A_1), IC1.J11 (VCCIO3B_1), IC1.L2 (VCCIO1A_2), IC1.L4 (VCCAUX_3), IC1.L14 (VCCIO3B_2), IC1.M11 (VCCAUX_4), IC1.N5 (VCCIO4B_1), IC1.N7 (VCCIO4B_2), IC1.N9 (VCCIO4A_1), IC1.N11 (VCCIO4A_2), IC1.P4 (VCCIO33_BL), R8.1, R10.1, TP5.1 (1_1), U2.5 (OUT), U5.5 (EN); also elsewhere on the board
2V8: C9.1, C17.1, R6.1, TP6.1 (1_1), U1.5 (OUT); also elsewhere on the board
3V3: C1.1, C32.1, C33.1, C35.1, C37.1, C58.1, IC1.N15 (VCCIO33_BR), L2.2, R21.1, TP3.1 (1_1), U1.1 (IN), U1.3 (EN), U2.1 (IN), U2.3 (EN); also elsewhere on the board
/ETHERNET_RTL8211F/POE_CT12: D1.3; also elsewhere on the board
/ETHERNET_RTL8211F/POE_CT36: D1.4; also elsewhere on the board
/ETHERNET_RTL8211F/POE_CT45: D3.3; also elsewhere on the board
/ETHERNET_RTL8211F/POE_CT78: D3.4; also elsewhere on the board
/Power/POE_VNEG: C52.2, D1.2 (-), D3.2 (-), R15.1, TP13.1 (1_1), U6.7 (NC), U6.11 (NC), U6.12 (NC), U6.14 (NC/VNEG), U6.15 (NC), U6.17 (NC), U6.20 (NC), U6.21 (EPAD/VNEG)
/Power/POE_VSS: C50.2, C53.2, C60.2, R14.2, R18.1, TP14.1 (1_1), U6.4 (FBL), U6.19 (VSS)
GND: C1.2, C2.2, C3.2, C4.2, C5.2, C6.2, C7.2, C8.2, C10.2, C11.2, C12.2, C13.2, C14.2, C15.2, C16.2, C17.2, C18.2, C19.2, C20.2, C21.2, C22.2, C23.2, C24.2, C25.2, C26.2, C27.2, C28.2, C29.2, C30.2, C31.2, C32.2, C33.2, C34.2, C35.2, C36.2, C37.2, C38.2, C39.2, C40.2, C41.2, C42.2, C44.2, C45.2, C46.2, C47.2, C48.2, C49.2, C51.2, C57.2, C58.2, C59.2, C61.2, C62.2, C63.2, C64.2, C65.2, IC1.A1 (GND_1), IC1.A15 (GND_2), IC1.D3 (GND_3), IC1.G6 (GND_4), IC1.G8 (GND_5), IC1.H7 (GND_6), IC1.H9 (GND_7), IC1.J6 (GND_8), IC1.J8 (GND_9), IC1.M13 (GND_10), IC1.R1 (GND_11), IC1.R15 (GND_12), L4.2, R7.2, R9.2, R12.2, R20.2, R22.2, R24.2, R25.2, TP7.1 (1_1), TP8.1 (1_1), TP9.1 (1_1), U1.2 (GND), U2.2 (GND), U3.1 (GND), U4.1 (GND), U5.1 (GND); also elsewhere on the board
unnamed: C43.2, R14.1
unnamed: D4.2 (A), L4.1, U6.18 (SWO)
unnamed: C9.2, R6.2, R7.1, U1.4 (FB)
unnamed: R8.2, R9.1, R10.2, U2.4 (FB)
unnamed: C54.1, L1.1, U3.2 (SW)
unnamed: C54.2, U3.6 (VBST)
unnamed: R19.2, R20.1, R25.1, U3.4 (VFB)
unnamed: C51.1, R17.2, U4.5 (EN)
unnamed: C55.1, L2.1, U4.2 (SW)
unnamed: C55.2, U4.6 (VBST)
unnamed: R21.2, R22.1, U4.4 (VFB)
unnamed: C56.1, L3.1, U5.2 (SW)
unnamed: C56.2, U5.6 (VBST)
unnamed: R23.2, R24.1, U5.4 (VFB)
unnamed: C43.1, U6.3 (EROUT)
unnamed: R11.2, R12.1, U6.2 (FBH)
unnamed: R18.2, U6.1 (ISNS), U6.8 (HSO)
unnamed: R15.2, U6.9 (RCL)
unnamed: R16.2, U6.6 (RDET)
unnamed: R13.2, U6.10 (RFREQ)
unnamed: C50.1, U6.5 (VDD)
USB_VBUS: D2.2 (A); also elsewhere on the board
VBUS: C44.1, C45.1, C46.1, C47.1, C48.1, C49.1, C52.1, C53.1, C60.1, C63.1, C64.1, C65.1, D1.1 (+), D2.1 (K), D3.1 (+), D4.1 (K), R11.1, R13.1, R16.1, R17.1, TP1.1 (1_1), U3.3 (VIN), U3.5 (EN), U4.3 (VIN), U5.3 (VIN), U6.13 (VPOS); also elsewhere on the board

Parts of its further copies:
C103: 1uF; C_0402_1005Metric; MPN CL05A105KA5NQNC; JLCPCB Library Basic

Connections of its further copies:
2V8: C103.1; also elsewhere on the board
/CAMERA_OV9282/CAM_AGND: C103.2; also elsewhere on the board

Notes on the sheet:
USB ALT POWER: VBUS ≈ USB_VBUS − VF (not 12 V)
3V3 BUCK — 3.302V nominal / 3A
IEEE 802.3af TYPE 1 PoE PD — SI3404 CLASS 3 / 12V OUTPUT
0V95 BUCK — 0.950V nominal / 3A
VCCIO1A / 1B — 1V8
0V95 FPGA LOCAL: 12x100n + 2x1u + 2x10u
1V8 FPGA LOCAL: 14x100n + 5x1u + 5x10u
VCCIO2A / 2B MIPI — 1V2
1V8 LDO — 1.8V nominal / 500mA
VCCA BR / BL / TL / TR BYPASS
2V8 LDO — 2.888V nominal / 500mA
1V2 BUCK — 1.198V nominal / 3A
R15: 49.9 ohm selects Si3404 Class-3 power classification.
VCCIO33 BYPASS: BL / TL / TR = 1V8; BR = 3V3
REDUCED 40-CAP FPGA DECOUPLING — REQUIRES >=4-LAYER LOW-INDUCTANCE PDN
VCCIO3A / 3B / 4A / 4B BYPASS — 1V8
